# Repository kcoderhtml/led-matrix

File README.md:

# Led matrix

Hopefully a cool led matrix ^-^

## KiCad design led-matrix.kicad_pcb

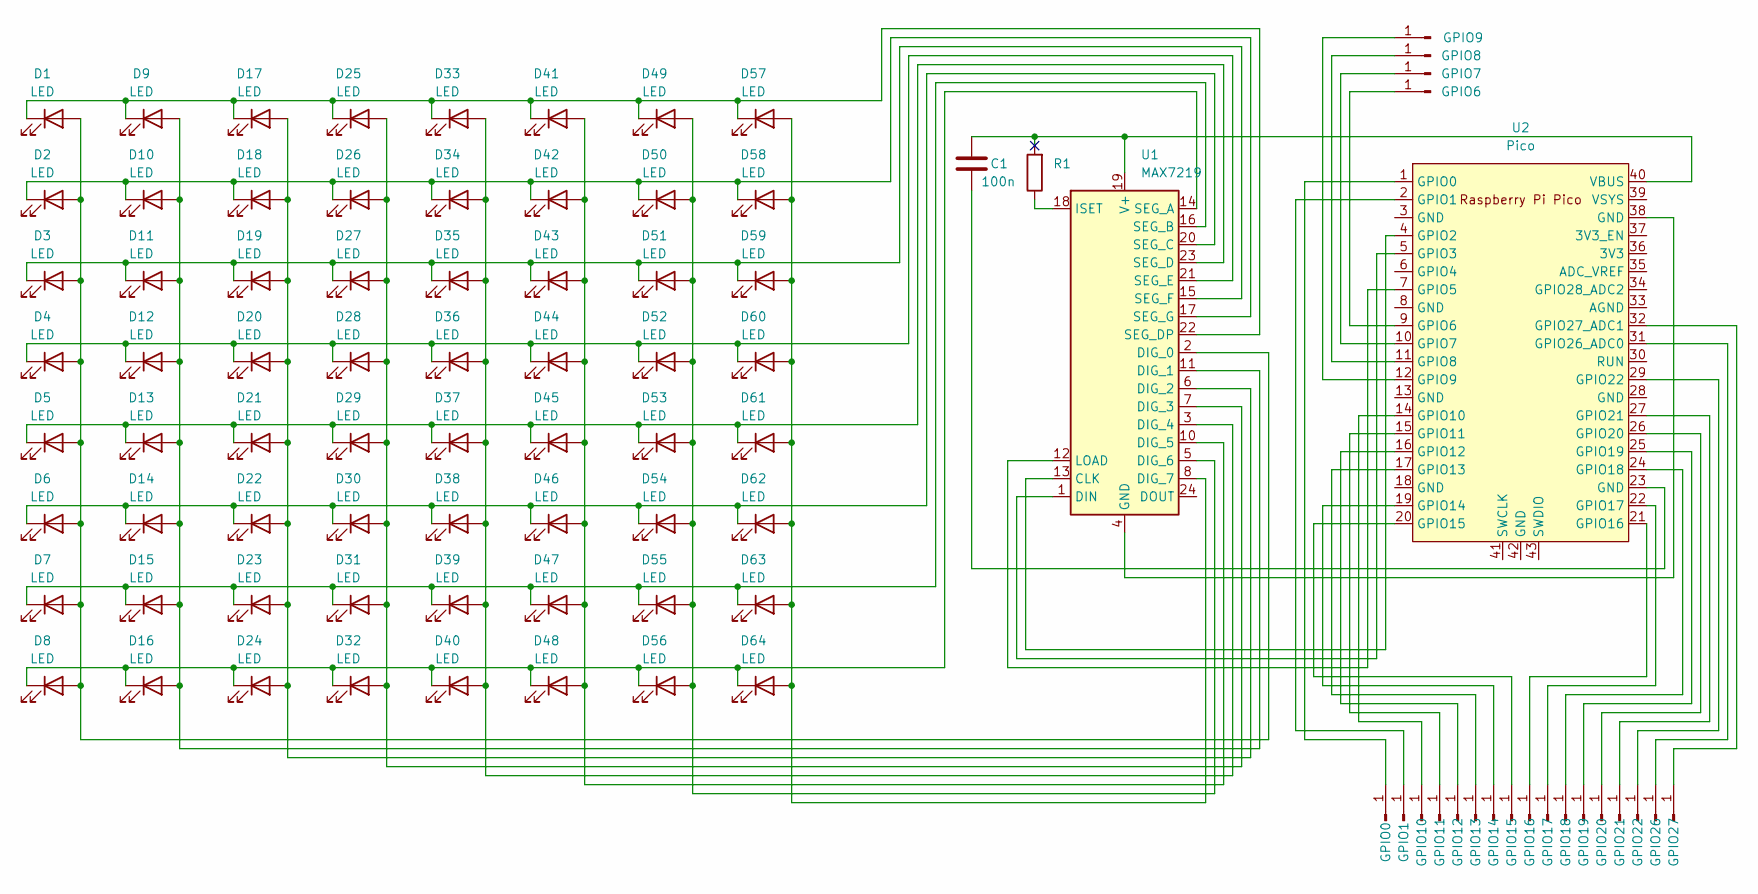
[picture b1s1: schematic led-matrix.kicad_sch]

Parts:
C1: 100n; C_Axial_L3.8mm_D2.6mm_P7.50mm_Horizontal
D1, D2, D3, D4, D5, D6, D7, D8, D9, D10, D11, D12, D13, D14, D15, D16, D17, D18, D19, D20, D21, D22, D23, D24, D25, D26, D27, D28, D29, D30, D31, D32, D33, D34, D35, D36, D37, D38, D39, D40, D41, D42, D43, D44, D45, D46, D47, D48, D49, D50, D51, D52, D53, D54, D55, D56, D57, D58, D59, D60, D61, D62, D63, D64: LED; LED_D3.0mm_Clear
GPIO0, GPIO1, GPIO6, GPIO7, GPIO8, GPIO9, GPIO10, GPIO11, GPIO12, GPIO13, GPIO14, GPIO15, GPIO16, GPIO17, GPIO18, GPIO19, GPIO20, GPIO21, GPIO22, GPIO26, GPIO27: Conn_01x01_Pin; Pin_D1.2mm_L11.3mm_W3.0mm_Flat
R1: 100k; R_Axial_DIN0204_L3.6mm_D1.6mm_P7.62mm_Horizontal
U1: MAX7219; DIL24
U2: Pico; RPi_Pico_SMD_TH

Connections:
unnamed: C1.2, U2.23 (GND)
unnamed: D1.2 (A), D2.2 (A), D3.2 (A), D4.2 (A), D5.2 (A), D6.2 (A), D7.2 (A), D8.2 (A), U1.2 (DIG_0)
unnamed: D1.1 (K), D9.1 (K), D17.1 (K), D25.1 (K), D33.1 (K), D41.1 (K), D49.1 (K), D57.1 (K), U1.22 (SEG_DP)
unnamed: D9.2 (A), D10.2 (A), D11.2 (A), D12.2 (A), D13.2 (A), D14.2 (A), D15.2 (A), D16.2 (A), U1.11 (DIG_1)
unnamed: D2.1 (K), D10.1 (K), D18.1 (K), D26.1 (K), D34.1 (K), D42.1 (K), D50.1 (K), D58.1 (K), U1.17 (SEG_G)
unnamed: D3.1 (K), D11.1 (K), D19.1 (K), D27.1 (K), D35.1 (K), D43.1 (K), D51.1 (K), D59.1 (K), U1.15 (SEG_F)
unnamed: D4.1 (K), D12.1 (K), D20.1 (K), D28.1 (K), D36.1 (K), D44.1 (K), D52.1 (K), D60.1 (K), U1.21 (SEG_E)
unnamed: D5.1 (K), D13.1 (K), D21.1 (K), D29.1 (K), D37.1 (K), D45.1 (K), D53.1 (K), D61.1 (K), U1.23 (SEG_D)
unnamed: D6.1 (K), D14.1 (K), D22.1 (K), D30.1 (K), D38.1 (K), D46.1 (K), D54.1 (K), D62.1 (K), U1.20 (SEG_C)
unnamed: D7.1 (K), D15.1 (K), D23.1 (K), D31.1 (K), D39.1 (K), D47.1 (K), D55.1 (K), D63.1 (K), U1.16 (SEG_B)
unnamed: D8.1 (K), D16.1 (K), D24.1 (K), D32.1 (K), D40.1 (K), D48.1 (K), D56.1 (K), D64.1 (K), U1.14 (SEG_A)
unnamed: D17.2 (A), D18.2 (A), D19.2 (A), D20.2 (A), D21.2 (A), D22.2 (A), D23.2 (A), D24.2 (A), U1.6 (DIG_2)
unnamed: D25.2 (A), D26.2 (A), D27.2 (A), D28.2 (A), D29.2 (A), D30.2 (A), D31.2 (A), D32.2 (A), U1.7 (DIG_3)
unnamed: D33.2 (A), D34.2 (A), D35.2 (A), D36.2 (A), D37.2 (A), D38.2 (A), D39.2 (A), D40.2 (A), U1.3 (DIG_4)
unnamed: D41.2 (A), D42.2 (A), D43.2 (A), D44.2 (A), D45.2 (A), D46.2 (A), D47.2 (A), D48.2 (A), U1.10 (DIG_5)
unnamed: D49.2 (A), D50.2 (A), D51.2 (A), D52.2 (A), D53.2 (A), D54.2 (A), D55.2 (A), D56.2 (A), U1.5 (DIG_6)
unnamed: D57.2 (A), D58.2 (A), D59.2 (A), D60.2 (A), D61.2 (A), D62.2 (A), D63.2 (A), D64.2 (A), U1.8 (DIG_7)
unnamed: GPIO0.1, U2.1 (GPIO0)
unnamed: GPIO1.1, U2.2 (GPIO1)
unnamed: GPIO6.1, U2.9 (GPIO6)
unnamed: GPIO7.1, U2.10 (GPIO7)
unnamed: GPIO8.1, U2.11 (GPIO8)
unnamed: GPIO9.1, U2.12 (GPIO9)
unnamed: GPIO10.1, U2.14 (GPIO10)
unnamed: GPIO11.1, U2.15 (GPIO11)
unnamed: GPIO12.1, U2.16 (GPIO12)
unnamed: GPIO13.1, U2.17 (GPIO13)
unnamed: GPIO14.1, U2.19 (GPIO14)
unnamed: GPIO15.1, U2.20 (GPIO15)
unnamed: GPIO16.1, U2.21 (GPIO16)
unnamed: GPIO17.1, U2.22 (GPIO17)
unnamed: GPIO18.1, U2.24 (GPIO18)
unnamed: GPIO19.1, U2.25 (GPIO19)
unnamed: GPIO20.1, U2.26 (GPIO20)
unnamed: GPIO21.1, U2.27 (GPIO21)
unnamed: GPIO22.1, U2.29 (GPIO22)
unnamed: GPIO26.1, U2.31 (GPIO26_ADC0)
unnamed: GPIO27.1, U2.32 (GPIO27_ADC1)
unnamed: U1.13 (CLK), U2.4 (GPIO2)
unnamed: U1.1 (DIN), U2.5 (GPIO3)
unnamed: U1.4 (GND), U1.9 (GND), U2.38 (GND)
unnamed: R1.1, U1.18 (ISET)
unnamed: U1.12 (LOAD), U2.7 (GPIO5)

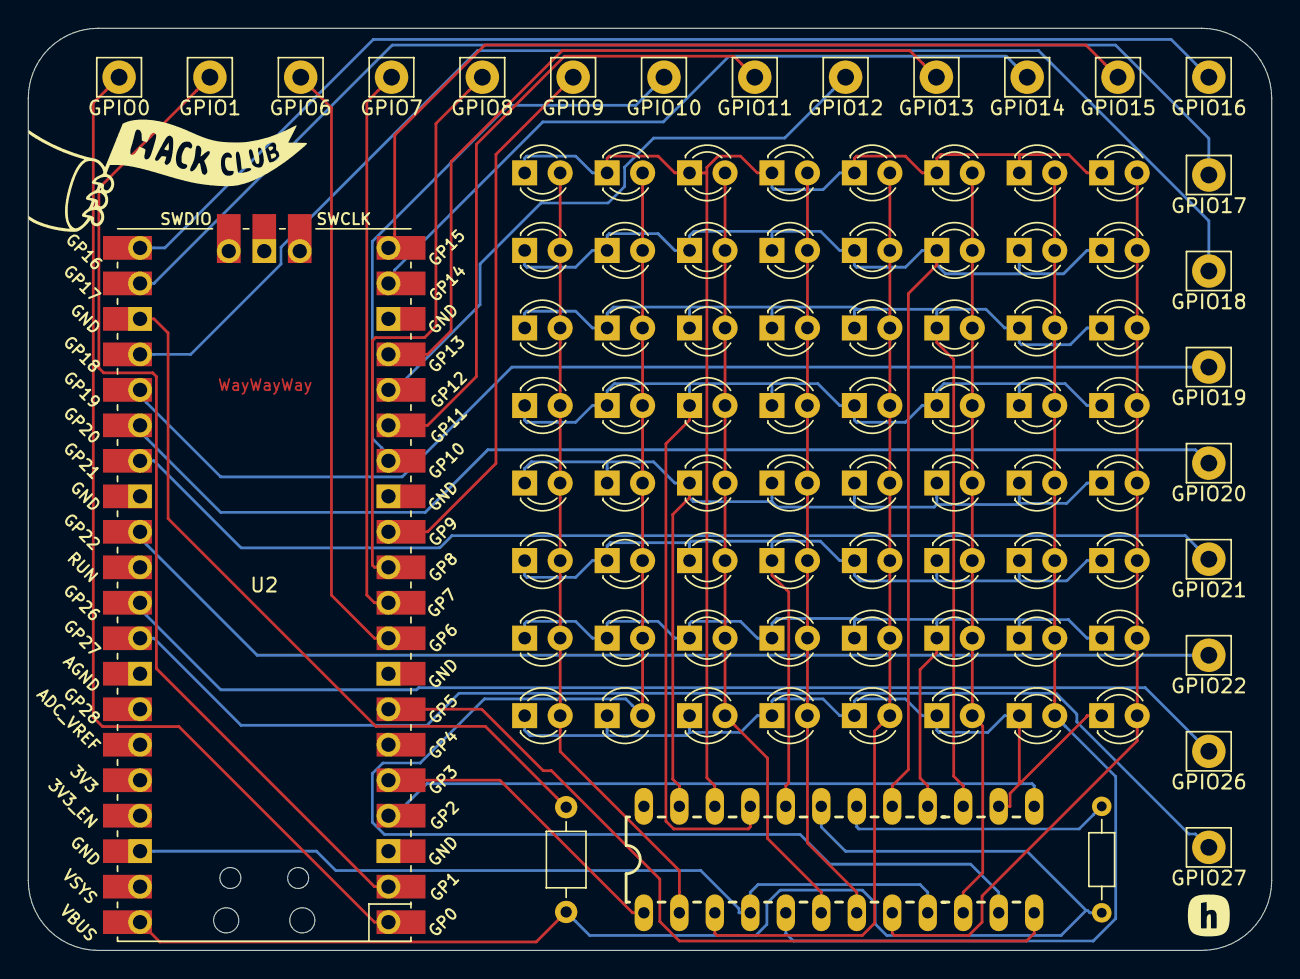
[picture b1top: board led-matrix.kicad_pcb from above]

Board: 2 copper layers, 89.0 x 66.0 mm, 92 parts (1 on the bottom side), 43 nets.

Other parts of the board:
face: LOGO
handlogo: LOGO
hclogo: LOGO

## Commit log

2024-08-03 feat: kicad init
2024-08-03 feat: added led matrix to schematic and add pico symbol
2024-08-03 chore: connect the matrix to the max7219
2024-08-03 feat: add grounding cap
2024-08-03 chore: set cap size to 100n
2024-08-03 feat: add touchpads
2024-08-03 chore: tighten up wires in the schematic
2024-08-03 feat: add gpio breakout
2024-08-03 feat: add pico footprint and max7219
2024-08-03 feat: create pcb
2024-08-03 feat: layout basic pcb design
2024-08-03 chore: align and center the gpio
2024-08-03 chore: make resister bigger and align max7219 and cap / resister
2024-08-03 chore: run erc
2024-08-03 chore: remove silkscreen layers for the leds and gpios
2024-08-03 chore: remove redundant grounds from gpio
2024-08-03 feat: change gpio names and move positions on pcb
2024-08-03 feat: add a 5mm fillet to the pcb
2024-08-03 feat: resize board outline
2024-08-04 feat: add image to pcb
2024-08-04 chore: move components for better routing
2024-08-04 feat: add routing from deeppcb
2024-08-04 chore: fix routing errors and run drc
2024-08-04 feat: prep for ordering and add jlc order mark
2024-10-04 feat: add logos
2024-10-05 chore: add initial code
2024-10-16 feat: add schematic
